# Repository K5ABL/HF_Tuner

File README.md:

# HF_Tuner
HF - 6m Antenna Tuner
This tuner was originally conceived as a companion for DIY transceiver kits like the QCX, uBITX and other amateur radio transceiver kits. It was designed to be self-contained and easy to integrate into an enclosure. All controls are located on a single plane for easy attachment to a front panel. It also has 4 corner mounting holes for secure mounting to a base plate or enclosure bottom. This design is now being offered as a kit through my company web site at http://www.celeritous.com The latest assembly instructions may also be obtained there or at http://www.K5ABL.com.

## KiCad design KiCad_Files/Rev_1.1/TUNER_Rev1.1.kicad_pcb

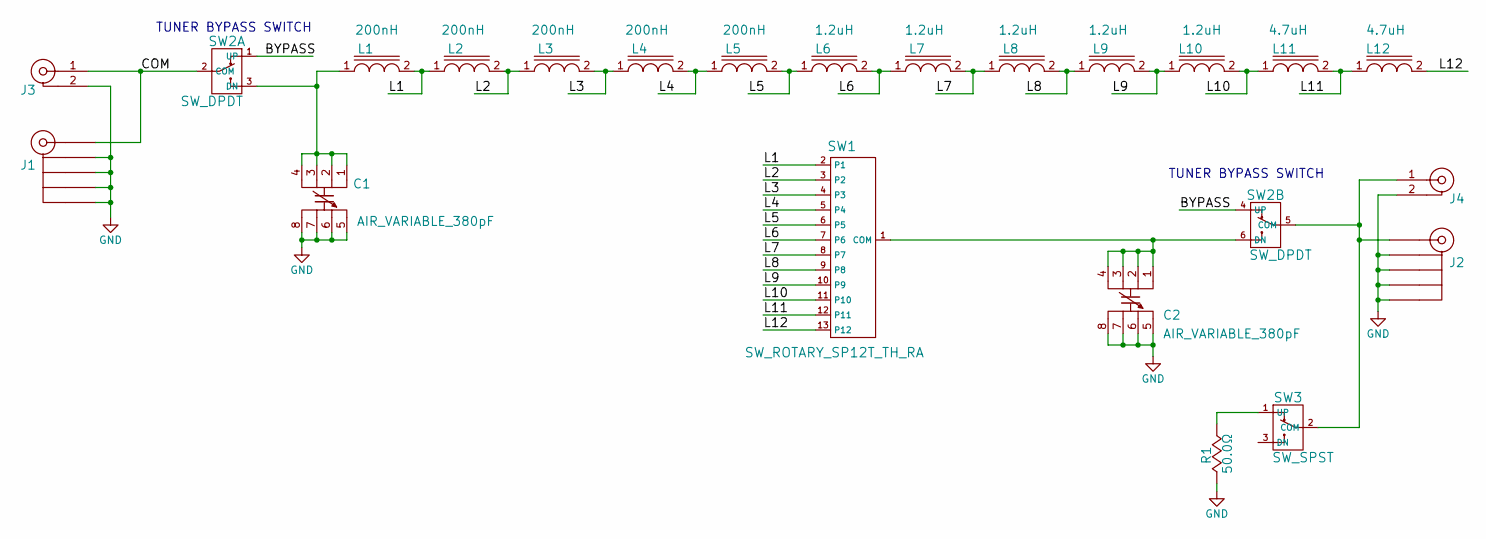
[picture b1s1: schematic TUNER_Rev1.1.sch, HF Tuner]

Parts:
C1, C2: AIR_VARIABLE_380pF; CAP_AIR_VARIABLE_360PF
J1, J2: RF_COAXIAL_PCB; CONNECTOR_RF_SMA_TH
J3, J4: RF_COAXIAL; CONN_BNC_RA
L1, L2, L3, L4, L5: 200nH; AXIAL_13mmLX4mmW
L6, L7, L8, L9, L10: 1.2uH; AXIAL_15mmLX6.5mmW
L11, L12: 4.7uH; AXIAL_15mmLX6.5mmW
R1: 50.0Ω; TO220_2
SW1: SW_ROTARY_SP12T_TH_RA; MODULE_12PST_SWITCH_RA
SW2: SW_DPDT; SW_DPDT_TOGGLE_RA
SW3: SW_SPST; SW_SPDT_TOGGLE_RA

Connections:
/BYPASS: SW2.1 (UP), SW2.4 (UP)
/COM: J1.1, J3.1, SW2.2 (COM)
/L1: L1.2, L2.1, SW1.2 (P1)
/L2: L2.2, L3.1, SW1.3 (P2)
/L3: L3.2, L4.1, SW1.4 (P3)
/L4: L4.2, L5.1, SW1.5 (P4)
/L5: L5.2, L6.1, SW1.6 (P5)
/L6: L6.2, L7.1, SW1.7 (P6)
/L7: L7.2, L8.1, SW1.8 (P7)
/L8: L8.2, L9.1, SW1.9 (P8)
/L9: L9.2, L10.1, SW1.10 (P9)
/L10: L10.2, L11.1, SW1.11 (P10)
/L11: L11.2, L12.1, SW1.12 (P11)
/L12: L12.2, SW1.13 (P12)
GND: C1.5, C1.6, C1.7, C1.8, C2.5, C2.6, C2.7, C2.8, J1.2, J1.3, J1.4, J1.5, J2.2, J2.3, J2.4, J2.5, J3.2, J4.2, R1.1
unnamed: C1.1, C1.2, C1.3, C1.4, L1.1, SW2.3 (DN)
unnamed: C2.1, C2.2, C2.3, C2.4, SW1.1 (COM), SW2.6 (DN)
unnamed: J2.1, J4.1, SW2.5 (COM), SW3.2 (COM)
unnamed: R1.2, SW3.1 (UP)

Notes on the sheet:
TUNER BYPASS SWITCH

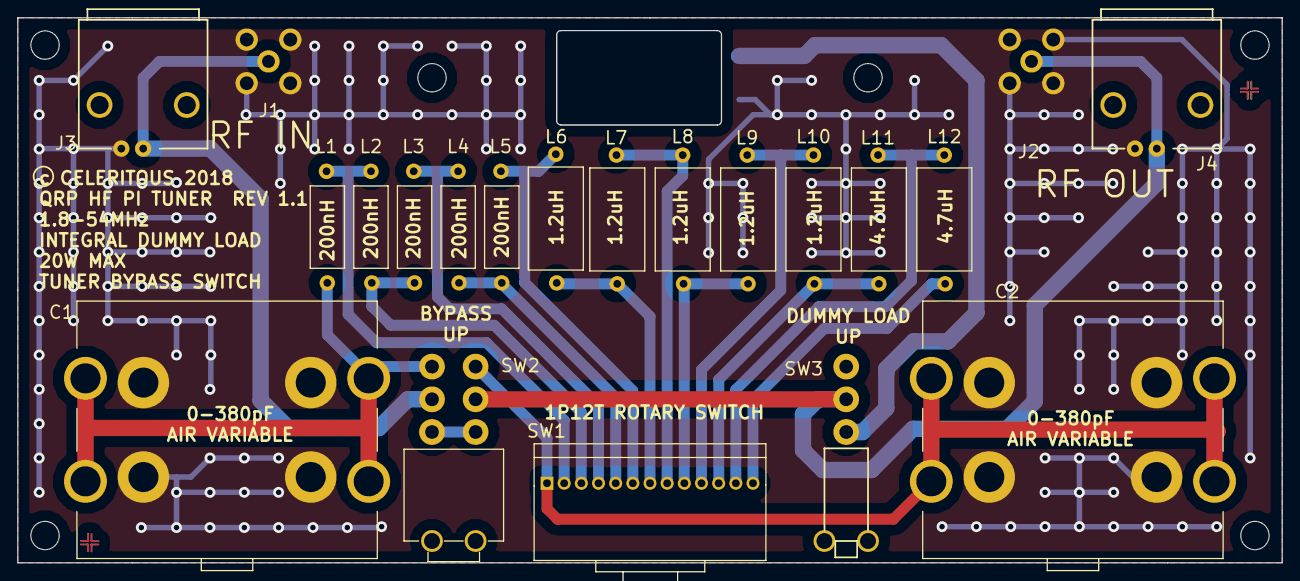
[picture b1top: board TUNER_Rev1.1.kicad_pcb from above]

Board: 2 copper layers, 147.3 x 63.5 mm, 26 parts (1 on the bottom side), 19 nets.

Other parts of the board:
REF1, REF2: FIDUCIAL_TOP
REF3, REF4: FIDUCIAL_BOTTOM

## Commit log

2019-09-23 Initial Commit - Assembly and Schematic
2019-09-23 Create Kicad_Files
2019-09-23 Rev 1.1 KiCad Files
